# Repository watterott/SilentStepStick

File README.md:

# SilentStepStick
The Silent-Step-Stick is a Stepper Motor Driver Board for 2-Phase Motors based on [Trinamic](https://www.trinamic.com) Motor Drivers.

* Hardware compatible with [StepStick](https://reprap.org/wiki/StepStick) and [Pololu A4988](https://www.pololu.com/product/1182)
* [Trinamic](https://www.trinamic.com) stepper motor driver (chopper drive / constant current drive) with
  * Automatic standby current reduction
  * **microPlyer** - microstep interpolator for increased smoothness of microstepping
  * **stealthChop** - for quiet operation and smooth motion
  * **spreadCycle** - highly dynamic motor control chopper
* Open-Source and released under the [Creative Commons Attribution Share-Alike License](https://creativecommons.org/licenses/by-sa/4.0/).
* **[Documentation on learn.watterott.com](https://learn.watterott.com)**

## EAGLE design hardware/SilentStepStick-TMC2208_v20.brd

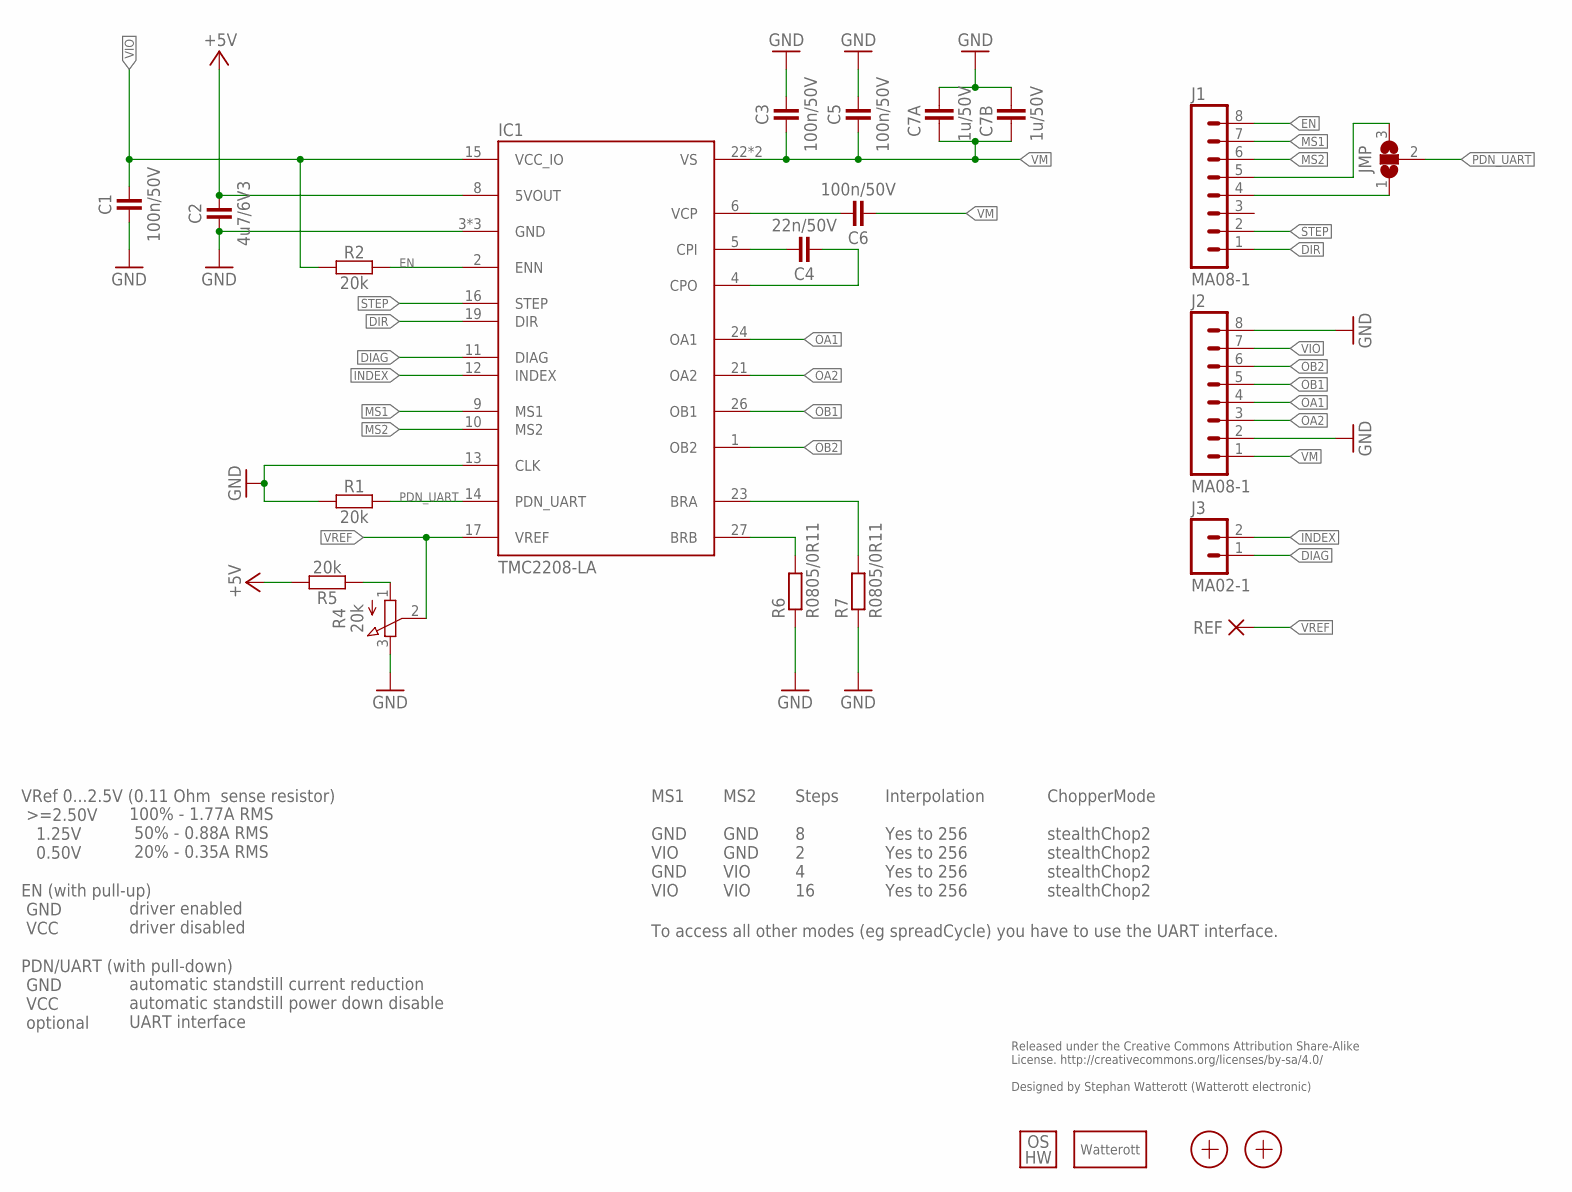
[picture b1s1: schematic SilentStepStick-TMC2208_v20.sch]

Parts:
C1, C3, C5, C6: 100n/50V; C0402
C2: 4u7/6V3; C0402
C4: 22n/50V; C0402
C7A: 1u/50V; C0805
C7B: 1u/50V; C1206
IC1: TMC2208-LA; QFN28-PAD
J1, J2: MA08-1
J3: MA02-1
JMP: JUMPER3-0402-NC; JUMPER3-0402_NC
LOGO3: LOGO_SPARK-2; SPARK_2MM
LOGO4: LOGO_OSHW-2; OSHW_2MM
R1, R2, R5: 20k; C0402
R4: 20k; POT_EVM3R
R6, R7: R0805/0R11; M0805
REF: PAD-0.6-1.1
X1, X2: PASSER-04; PASSER_04MM

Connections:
+5V: C2.2, IC1.8 (5VOUT), R5.2
BRA: IC1.23 (BRA), R7.2
BRB: IC1.27 (BRB), R6.2
CPI: C4.2, IC1.5 (CPI)
CPO: C4.1, IC1.4 (CPO)
DIAG: IC1.11 (DIAG), J3.1
DIR: IC1.19 (DIR), J1.1
EN: IC1.2 (ENN), J1.8, R2.2
GND: C1.1, C2.1, C3.2, C5.2, C7A.2, C7B.2, IC1.3 (GND), IC1.13 (CLK), IC1.18 (GND), IC1.TP (GND), J2.2, J2.8, R1.1, R4.3 (E), R6.1, R7.1
INDEX: IC1.12 (INDEX), J3.2
MS1: IC1.9 (MS1), J1.7
MS2: IC1.10 (MS2), J1.6
unnamed: J1.5, JMP.3
unnamed: J1.4, JMP.1
OA1: IC1.24 (OA1), J2.4
OA2: IC1.21 (OA2), J2.3
OB1: IC1.26 (OB1), J2.5
OB2: IC1.1 (OB2), J2.6
PDN_UART: IC1.14 (PDN_UART), JMP.2, R1.2
STEP: IC1.16 (STEP), J1.2
VCP: C6.2, IC1.6 (VCP)
VIO: C1.2, IC1.15 (VCC_IO), J2.7, R2.1
VM: C3.1, C5.1, C6.1, C7A.1, C7B.1, IC1.22 (VS), IC1.28 (VS), J2.1
VREF: IC1.17 (VREF), R4.2 (S), REF.1
VREF1: R4.1 (A), R5.1

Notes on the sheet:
Released under the Creative Commons Attribution Share-Alike License. http://creativecommons.org/licenses/by-sa/4.0/ Designed by Stephan Watterott (Watterott electronic)
VRef 0...2.5V (0.11 Ohm sense resistor) >=2.50V 1.25V 0.50V EN (with pull-up) GND VCC PDN/UART (with pull-down) GND VCC optional
100% - 1.77A RMS 50% - 0.88A RMS 20% - 0.35A RMS driver enabled driver disabled automatic standstill current reduction automatic standstill power down disable UART interface
MS1 GND VIO GND VIO
MS2 GND GND VIO VIO
Steps 8 2 4 16
Interpolation Yes to 256 Yes to 256 Yes to 256 Yes to 256
ChopperMode stealthChop2 stealthChop2 stealthChop2 stealthChop2
To access all other modes (eg spreadCycle) you have to use the UART interface.

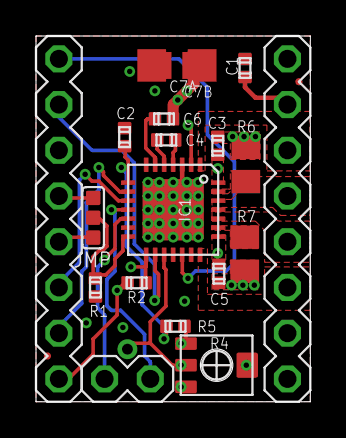
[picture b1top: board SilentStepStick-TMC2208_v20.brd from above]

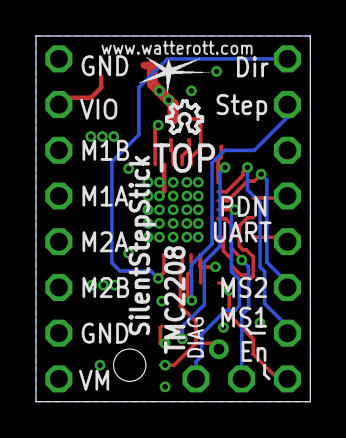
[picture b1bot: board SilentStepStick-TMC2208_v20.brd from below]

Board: 4 copper layers, 15.2 x 20.3 mm, 24 parts (2 on the bottom side), 25 nets.

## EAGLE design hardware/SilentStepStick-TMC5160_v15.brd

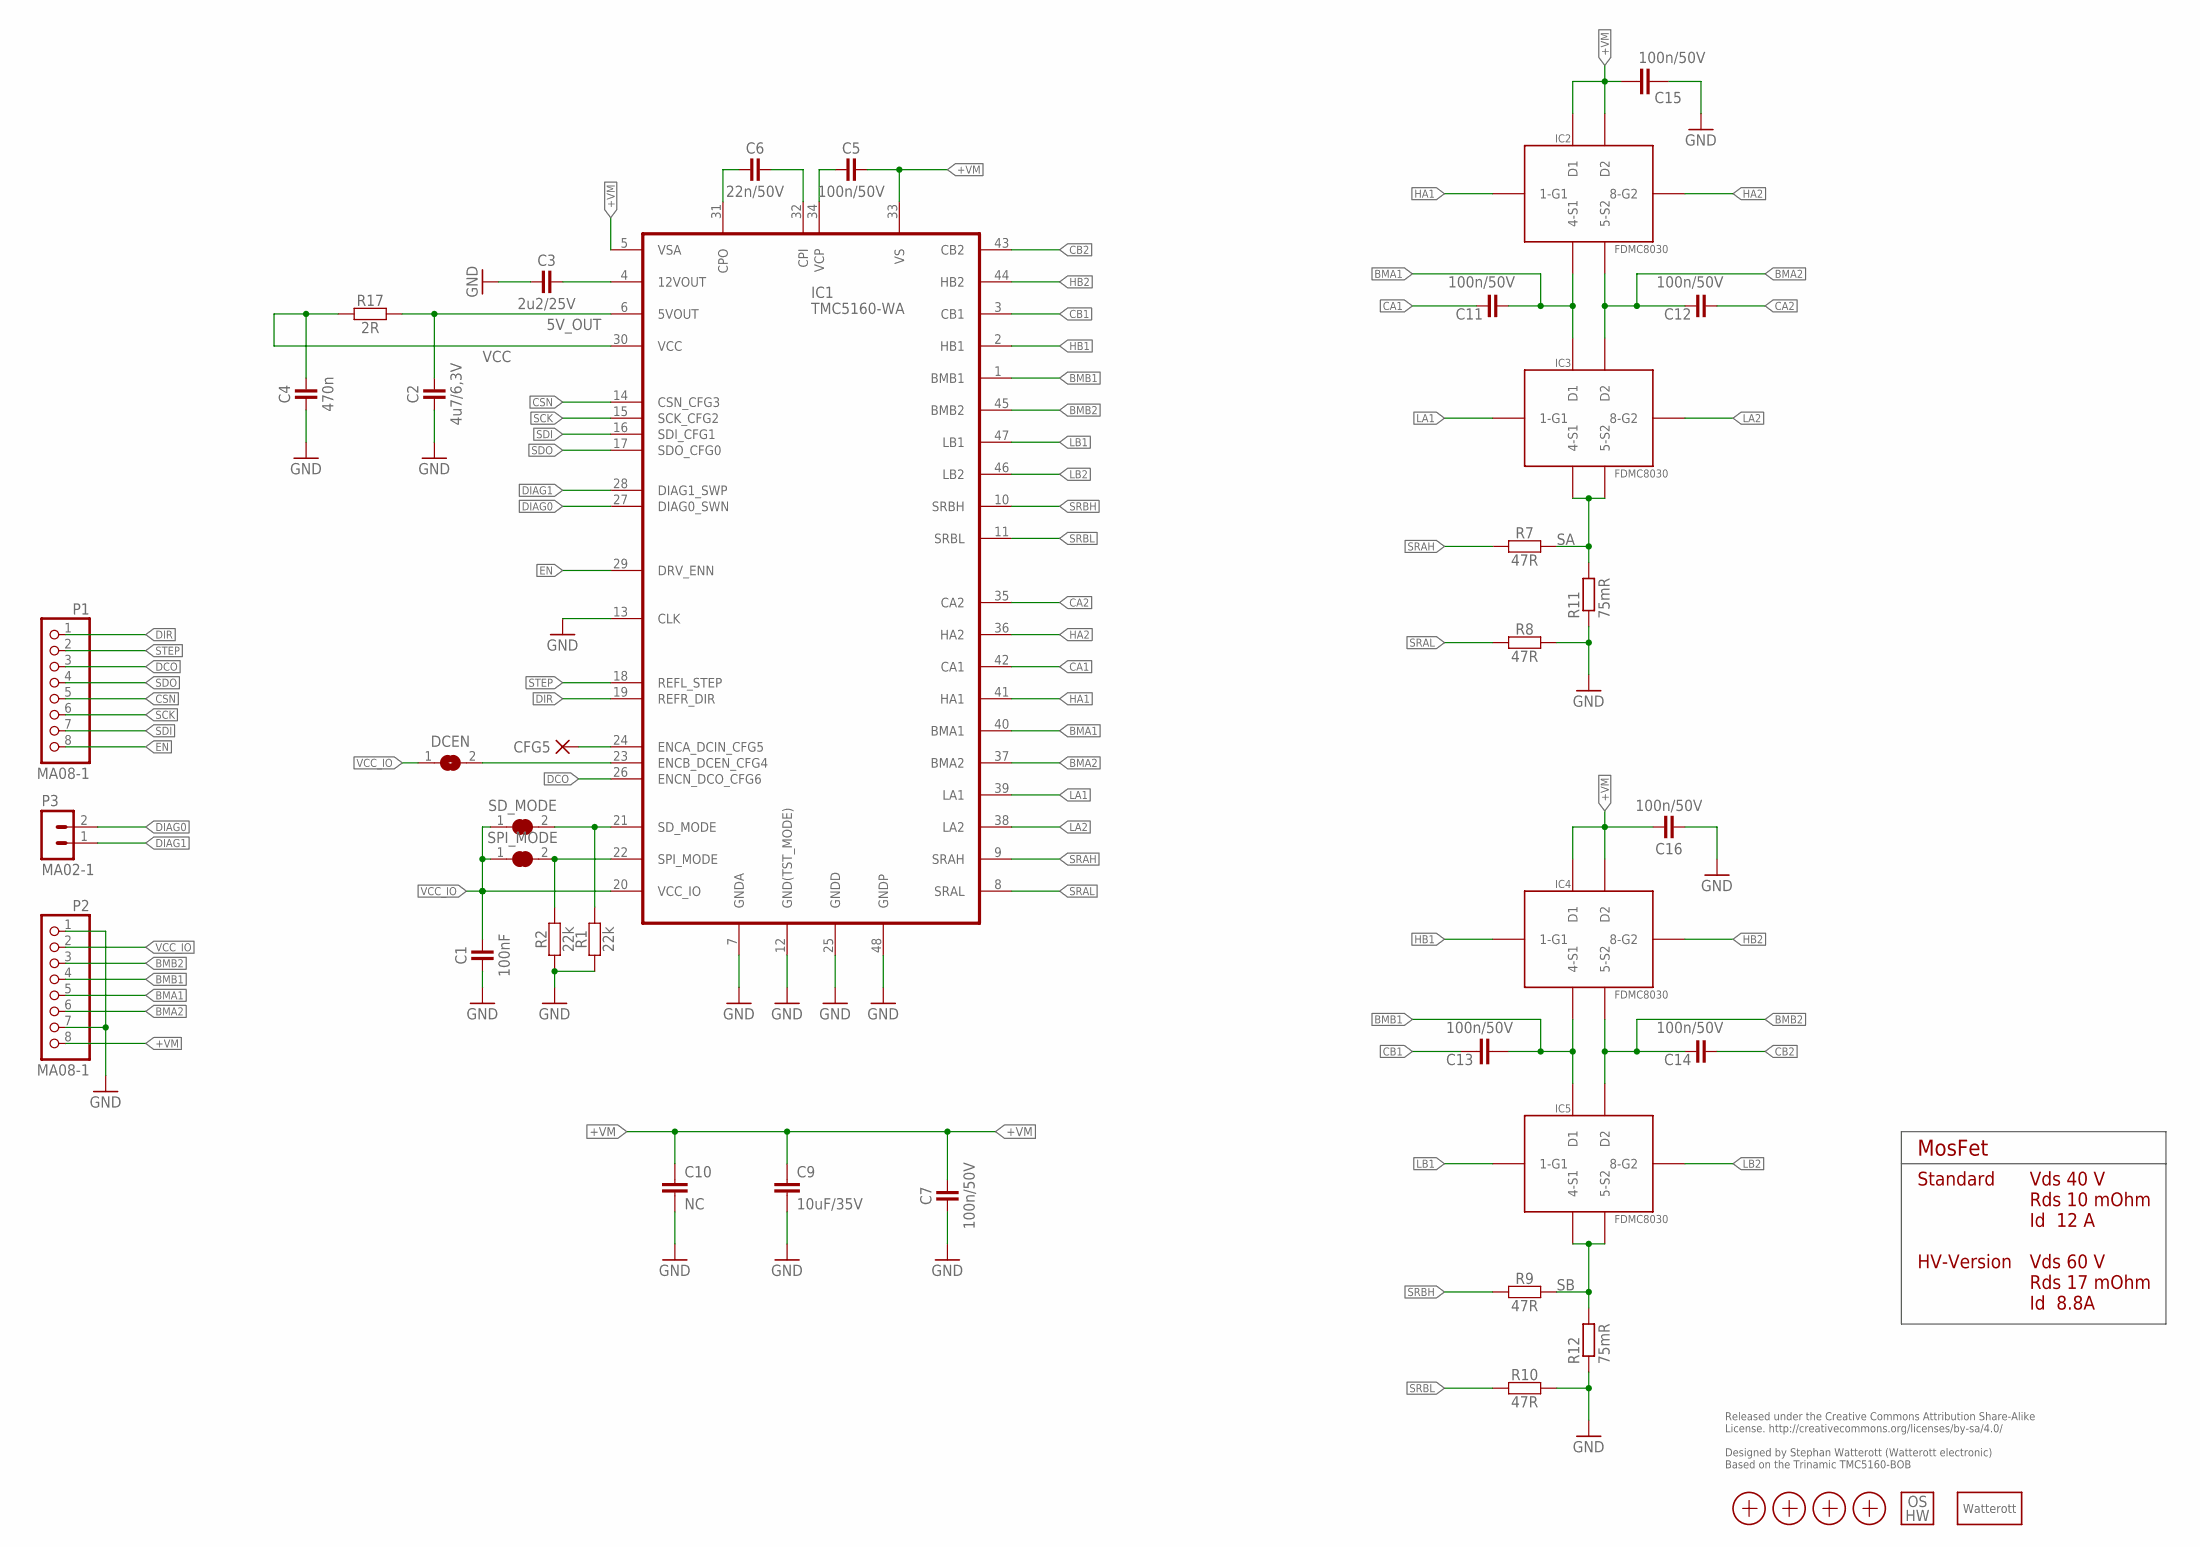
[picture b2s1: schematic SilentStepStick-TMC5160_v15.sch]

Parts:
C1: 100nF; C0402
C2: 4u7/6,3V; C0402
C3: 2u2/25V; C0402
C4: 470n; C0402
C5, C7, C11, C12, C13, C14, C15, C16: 100n/50V; C0402
C6: 22n/50V; C0402
C9: 10uF/35V; C0805
C10: NC; C0805
CFG5: PAD-0.7_NC
DCEN: JUMPER2-0402-NC; JUMPER2-0402_NC
IC1: TMC5160-WA; VQFN56(47)_8.0X8.0X0.9MM_0.5P_EP
IC2, IC3, IC4, IC5: FDMC8030; 8-POWERWDFN
LOGO1: LOGO_SPARK-2; SPARK_2MM
LOGO2: LOGO_OSHW-2; OSHW_2MM
P1, P2: MA08-1; 1X08-S
P3: MA02-1
R1, R2: 22k; C0201
R7, R8, R9, R10: 47R; C0402
R11, R12: 75mR; R1206
R17: 2R; C0402
SD_MODE: JUMPER2-0402-NC; JUMPER2-0402_NC
SPI_MODE: JUMPER2-0402-NC; JUMPER2-0402_NC
X1, X2, X3, X4: PASSER-04; PASSER_04MM

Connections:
5V_OUT: C2.2, IC1.6 (5VOUT), R17.2
+VM: C5.2, C7.2, C9.1, C10.1, C15.2, C16.2, IC1.5 (VSA), IC1.33 (VS), IC2.P$D1 (D1), IC2.P$D2 (D2), IC4.P$D1 (D1), IC4.P$D2 (D2), P2.8
BMA1: C11.1, IC1.40 (BMA1), IC2.P$4 (4-S1), IC3.P$D1 (D1), P2.5
BMA2: C12.2, IC1.37 (BMA2), IC2.P$5 (5-S2), IC3.P$D2 (D2), P2.6
BMB1: C13.1, IC1.1 (BMB1), IC4.P$4 (4-S1), IC5.P$D1 (D1), P2.4
BMB2: C14.2, IC1.45 (BMB2), IC4.P$5 (5-S2), IC5.P$D2 (D2), P2.3
CA1: C11.2, IC1.42 (CA1)
CA2: C12.1, IC1.35 (CA2)
CB1: C13.2, IC1.3 (CB1)
CB2: C14.1, IC1.43 (CB2)
CSN: IC1.14 (CSN_CFG3), P1.5
DCEN: DCEN.2, IC1.23 (ENCB_DCEN_CFG4)
DCIN: CFG5.1, IC1.24 (ENCA_DCIN_CFG5)
DCO: IC1.26 (ENCN_DCO_CFG6), P1.3
DIAG0: IC1.27 (DIAG0_SWN), P3.2
DIAG1: IC1.28 (DIAG1_SWP), P3.1
DIR: IC1.19 (REFR_DIR), P1.1
EN: IC1.29 (DRV_ENN), P1.8
GND: C1.1, C2.1, C3.1, C4.1, C7.1, C9.2, C10.2, C15.1, C16.1, IC1.7 (GNDA), IC1.12 (GND(TST_MODE)), IC1.13 (CLK), IC1.25 (GNDD), IC1.48 (GNDP), P2.1, P2.7, R1.1, R2.1, R8.2, R10.2, R11.1, R12.1
HA1: IC1.41 (HA1), IC2.P$1 (1-G1)
HA2: IC1.36 (HA2), IC2.P$8 (8-G2)
HB1: IC1.2 (HB1), IC4.P$1 (1-G1)
HB2: IC1.44 (HB2), IC4.P$8 (8-G2)
LA1: IC1.39 (LA1), IC3.P$1 (1-G1)
LA2: IC1.38 (LA2), IC3.P$8 (8-G2)
LB1: IC1.47 (LB1), IC5.P$1 (1-G1)
LB2: IC1.46 (LB2), IC5.P$8 (8-G2)
unnamed: C6.2, IC1.32 (CPI)
unnamed: C6.1, IC1.31 (CPO)
unnamed: C3.2, IC1.4 (12VOUT)
unnamed: C5.1, IC1.34 (VCP)
SA: IC3.P$4 (4-S1), IC3.P$5 (5-S2), R7.2, R11.2
SB: IC5.P$4 (4-S1), IC5.P$5 (5-S2), R9.2, R12.2
SCK: IC1.15 (SCK_CFG2), P1.6
SD: IC1.21 (SD_MODE), R1.2, SD_MODE.2
SDI: IC1.16 (SDI_CFG1), P1.7
SDO: IC1.17 (SDO_CFG0), P1.4
SPI: IC1.22 (SPI_MODE), R2.2, SPI_MODE.2
SRAH: IC1.9 (SRAH), R7.1
SRAL: IC1.8 (SRAL), R8.1
SRBH: IC1.10 (SRBH), R9.1
SRBL: IC1.11 (SRBL), R10.1
STEP: IC1.18 (REFL_STEP), P1.2
VCC: C4.2, IC1.30 (VCC), R17.1
VCC_IO: C1.2, DCEN.1, IC1.20 (VCC_IO), P2.2, SD_MODE.1, SPI_MODE.1

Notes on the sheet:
Released under the Creative Commons Attribution Share-Alike License. http://creativecommons.org/licenses/by-sa/4.0/ Designed by Stephan Watterott (Watterott electronic) Based on the Trinamic TMC5160-BOB
Vds 40 V Rds 10 mOhm Id 12 A Vds 60 V Rds 17 mOhm Id 8.8A
MosFet
Standard HV-Version

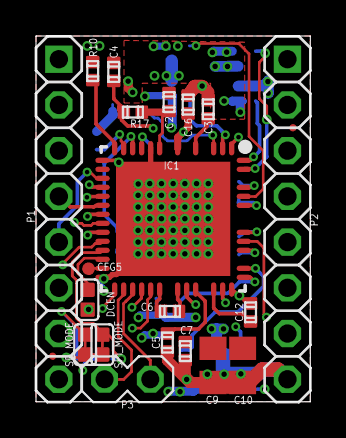
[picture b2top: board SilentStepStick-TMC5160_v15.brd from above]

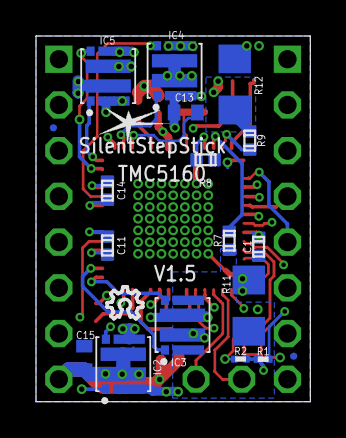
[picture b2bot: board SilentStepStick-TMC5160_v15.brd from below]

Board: 6 copper layers, 15.2 x 20.3 mm, 42 parts (20 on the bottom side), 45 nets.

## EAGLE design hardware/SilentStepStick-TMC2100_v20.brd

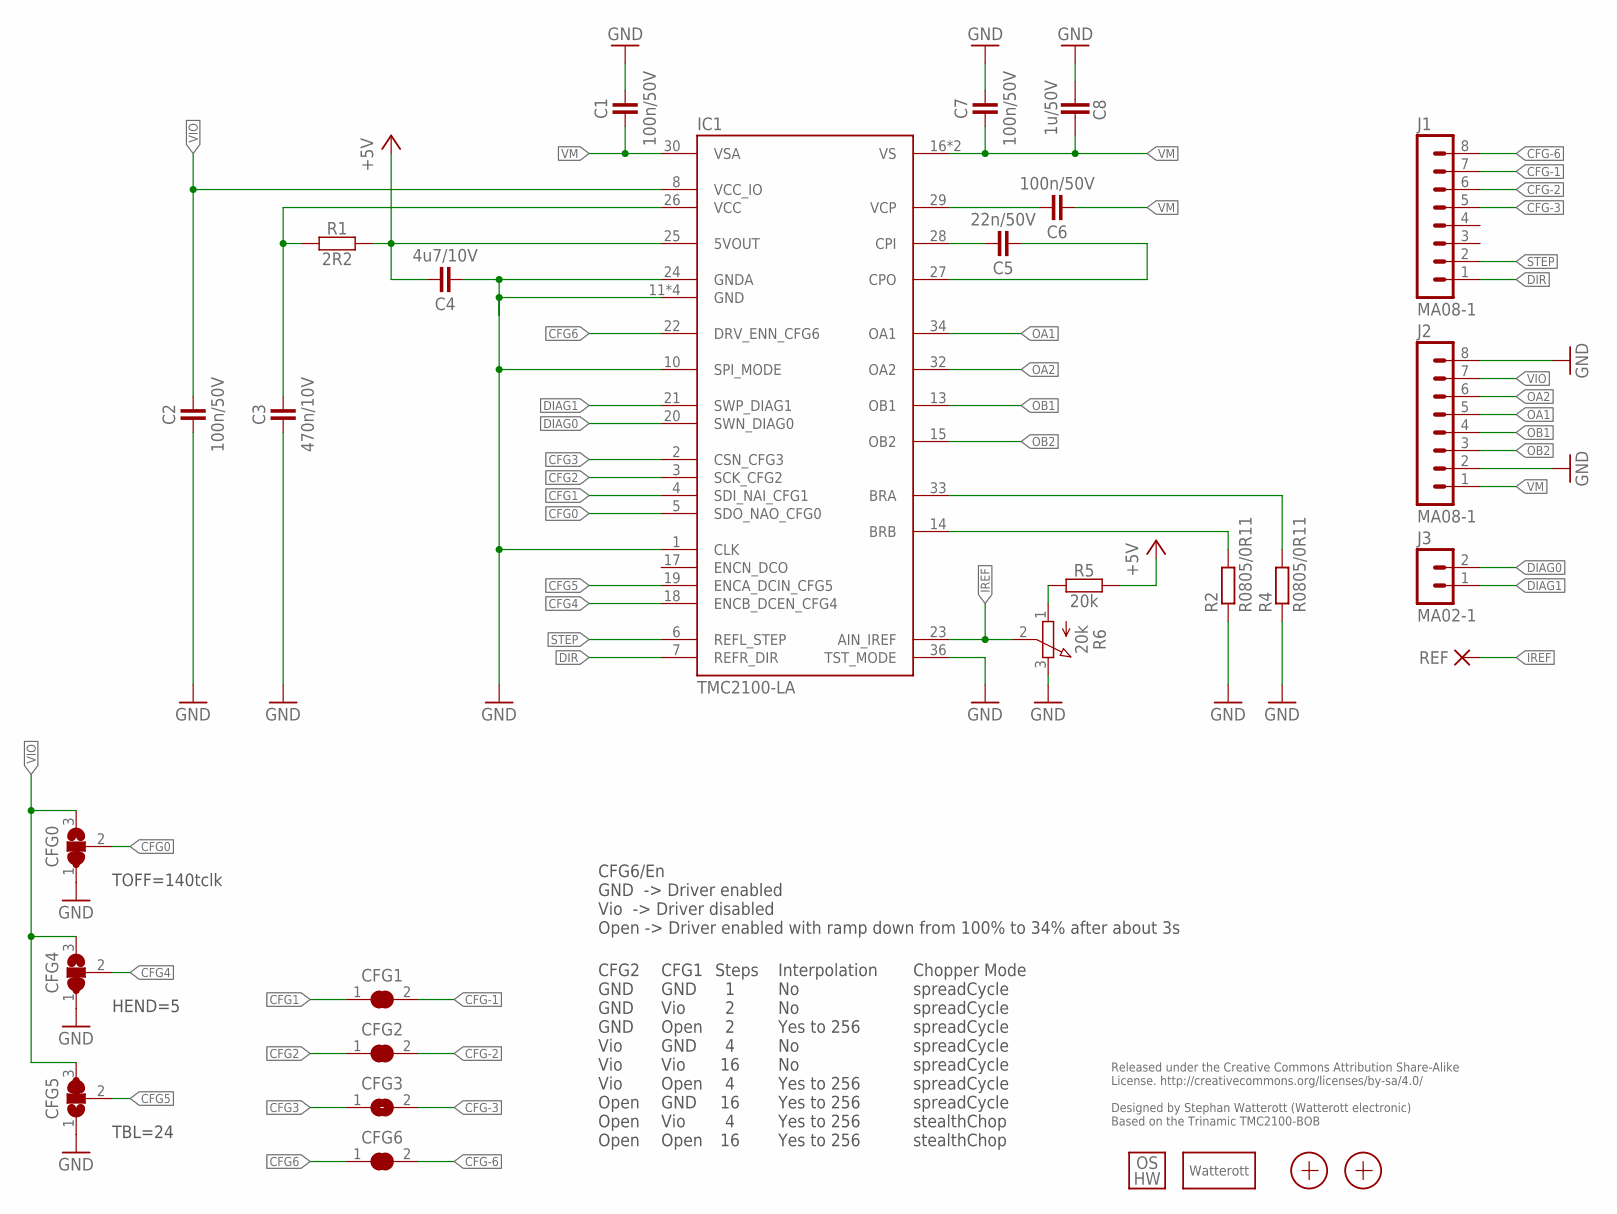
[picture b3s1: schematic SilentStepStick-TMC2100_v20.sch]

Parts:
C1, C2, C6, C7: 100n/50V; C0402
C3: 470n/10V; C0402
C4: 4u7/10V; C0402
C5: 22n/50V; C0402
C8: 1u/50V; C0603
CFG0, CFG4, CFG5: JUMPER3-0201
CFG1, CFG2, CFG3, CFG6: JUMPER2-0201
IC1: TMC2100-LA; QFN36-PAD
J1, J2: MA08-1
J3: MA02-1
LOGO3: LOGO_SPARK-2; SPARK_2MM
LOGO4: LOGO_OSHW-2; OSHW_2MM
R1: 2R2; C0402
R2, R4: R0805/0R11; M0805
R5: 20k; C0402
R6: 20k; POT_EVM3R
REF: PAD-0.6-1.1
X1, X2: PASSER-07; PASSER_07MM

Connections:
+5V: C4.2, IC1.25 (5VOUT), R1.2, R5.2
BRA: IC1.33 (BRA), R4.2
BRB: IC1.14 (BRB), R2.2
CFG0: CFG0.2, IC1.5 (SDO_NAO_CFG0)
CFG1: CFG1.1, IC1.4 (SDI_NAI_CFG1)
CFG2: CFG2.1, IC1.3 (SCK_CFG2)
CFG3: CFG3.1, IC1.2 (CSN_CFG3)
CFG4: CFG4.2, IC1.18 (ENCB_DCEN_CFG4)
CFG5: CFG5.2, IC1.19 (ENCA_DCIN_CFG5)
CFG6: CFG6.1, IC1.22 (DRV_ENN_CFG6)
CFG-1: CFG1.2, J1.7
CFG-2: CFG2.2, J1.6
CFG-3: CFG3.2, J1.5
CFG-6: CFG6.2, J1.8
CPI: C5.2, IC1.28 (CPI)
CPO: C5.1, IC1.27 (CPO)
DIAG0: IC1.20 (SWN_DIAG0), J3.2
DIAG1: IC1.21 (SWP_DIAG1), J3.1
DIR: IC1.7 (REFR_DIR), J1.1
GND: C1.2, C2.1, C3.1, C4.1, C7.2, C8.2, CFG0.1, CFG4.1, CFG5.1, IC1.1 (CLK), IC1.10 (SPI_MODE), IC1.11 (GND), IC1.12 (GND), IC1.24 (GNDA), IC1.35 (GND), IC1.36 (TST_MODE), IC1.TP (GND), J2.2, J2.8, R2.1, R4.1, R6.3 (E)
IREF: IC1.23 (AIN_IREF), R6.2 (S), REF.1
OA1: IC1.34 (OA1), J2.5
OA2: IC1.32 (OA2), J2.6
OB1: IC1.13 (OB1), J2.4
OB2: IC1.15 (OB2), J2.3
STEP: IC1.6 (REFL_STEP), J1.2
VCC: C3.2, IC1.26 (VCC), R1.1
VCP: C6.2, IC1.29 (VCP)
VIO: C2.2, CFG0.3, CFG4.3, CFG5.3, IC1.8 (VCC_IO), J2.7
VM: C1.1, C6.1, C7.1, C8.1, IC1.16 (VS), IC1.30 (VSA), IC1.31 (VS), J2.1
VREF1: R5.1, R6.1 (A)

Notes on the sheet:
Released under the Creative Commons Attribution Share-Alike License. http://creativecommons.org/licenses/by-sa/4.0/ Designed by Stephan Watterott (Watterott electronic) Based on the Trinamic TMC2100-BOB
CFG6/En GND -> Driver enabled Vio -> Driver disabled Open -> Driver enabled with ramp down from 100% to 34% after about 3s
CFG2 GND GND GND Vio Vio Vio Open Open Open
CFG1 GND Vio Open GND Vio Open GND Vio Open
Steps 1 2 2 4 16 4 16 4 16
Interpolation No No Yes to 256 No No Yes to 256 Yes to 256 Yes to 256 Yes to 256
Chopper Mode spreadCycle spreadCycle spreadCycle spreadCycle spreadCycle spreadCycle spreadCycle stealthChop stealthChop
TOFF=140tclk
HEND=5
TBL=24

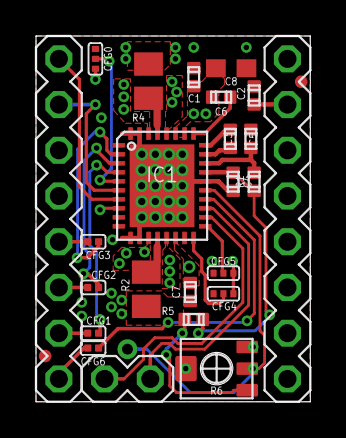
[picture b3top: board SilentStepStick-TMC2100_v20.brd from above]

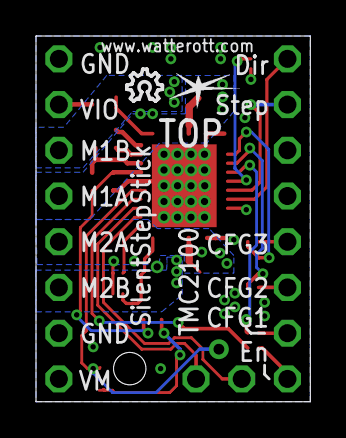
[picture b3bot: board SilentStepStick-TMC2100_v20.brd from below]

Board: 4 copper layers, 15.2 x 20.3 mm, 29 parts (2 on the bottom side), 31 nets.

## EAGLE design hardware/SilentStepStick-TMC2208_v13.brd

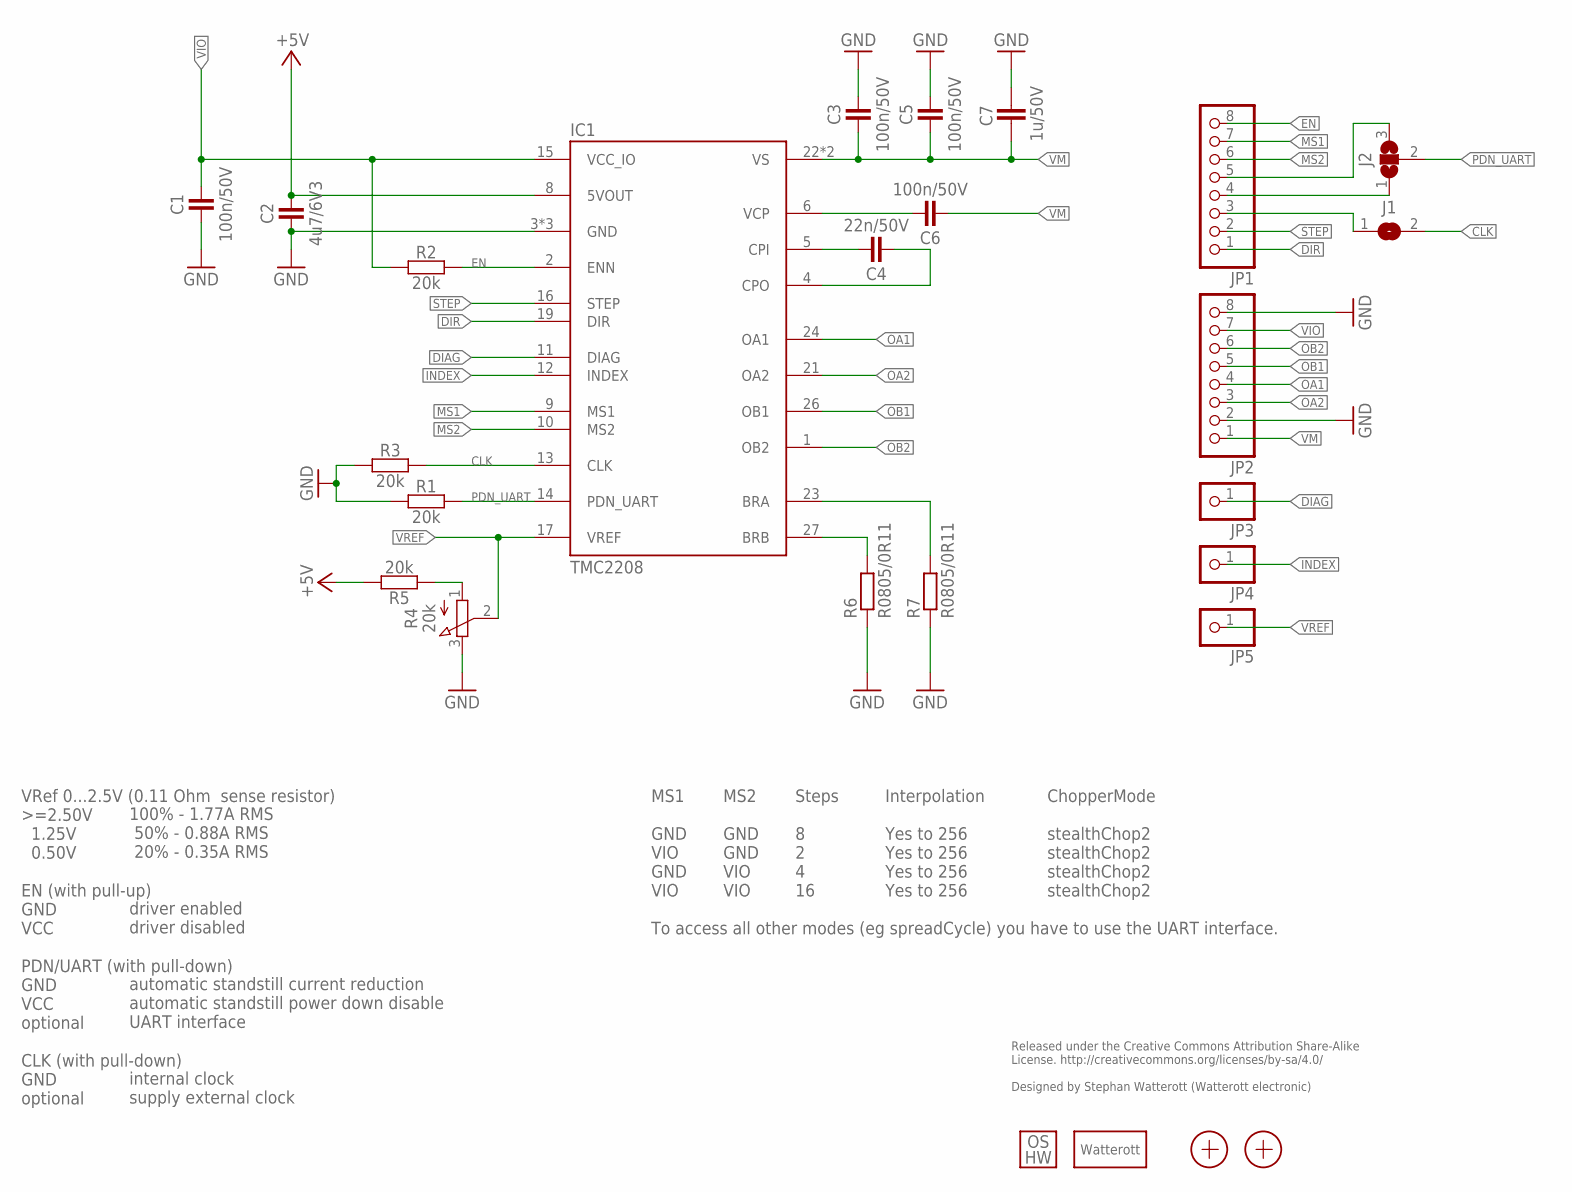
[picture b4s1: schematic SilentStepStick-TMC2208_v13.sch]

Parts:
C1, C3, C5, C6: 100n/50V; C0402
C2: 4u7/6V3; C0402
C4: 22n/50V; C0402
C7: 1u/50V; C0805
IC1: TMC2208; QFN28-PAD
J1: JUMPER2-0402
J2: JUMPER3-0402-NC; JUMPER3-0402_NC
JP1, JP2: PINHD-1X08_2.54-S; 1X08-S
JP3, JP4, JP5: PINHD-1X1; 1X01
LOGO3: LOGO_SPARK-2; SPARK_2MM
LOGO4: LOGO_OSHW-2; OSHW_2MM
R1, R2, R3, R5: 20k; C0402
R4: 20k; POT_EVM3R
R6, R7: R0805/0R11; M0805
X1, X2: PASSER-04; PASSER_04MM

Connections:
+5V: C2.2, IC1.8 (5VOUT), R5.2
BRA: IC1.23 (BRA), R7.2
BRB: IC1.27 (BRB), R6.2
CLK: IC1.13 (CLK), J1.2, R3.2
CPI: C4.2, IC1.5 (CPI)
CPO: C4.1, IC1.4 (CPO)
DIAG: IC1.11 (DIAG), JP3.1
DIR: IC1.19 (DIR), JP1.1
EN: IC1.2 (ENN), JP1.8, R2.2
GND: C1.1, C2.1, C3.2, C5.2, C7.2, IC1.3 (GND), IC1.18 (GND), IC1.TP (GND), JP2.2, JP2.8, R1.1, R3.1, R4.3 (E), R6.1, R7.1
INDEX: IC1.12 (INDEX), JP4.1
MS1: IC1.9 (MS1), JP1.7
MS2: IC1.10 (MS2), JP1.6
unnamed: J2.3, JP1.5
unnamed: J1.1, JP1.3
unnamed: J2.1, JP1.4
OA1: IC1.24 (OA1), JP2.4
OA2: IC1.21 (OA2), JP2.3
OB1: IC1.26 (OB1), JP2.5
OB2: IC1.1 (OB2), JP2.6
PDN_UART: IC1.14 (PDN_UART), J2.2, R1.2
STEP: IC1.16 (STEP), JP1.2
VCP: C6.2, IC1.6 (VCP)
VIO: C1.2, IC1.15 (VCC_IO), JP2.7, R2.1
VM: C3.1, C5.1, C6.1, C7.1, IC1.22 (VS), IC1.28 (VS), JP2.1
VREF: IC1.17 (VREF), JP5.1, R4.2 (S)
VREF1: R4.1 (A), R5.1

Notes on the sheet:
Released under the Creative Commons Attribution Share-Alike License. http://creativecommons.org/licenses/by-sa/4.0/ Designed by Stephan Watterott (Watterott electronic)
VRef 0...2.5V (0.11 Ohm sense resistor) >=2.50V 1.25V 0.50V EN (with pull-up) GND VCC PDN/UART (with pull-down) GND VCC optional CLK (with pull-down) GND optional
100% - 1.77A RMS 50% - 0.88A RMS 20% - 0.35A RMS driver enabled driver disabled automatic standstill current reduction automatic standstill power down disable UART interface internal clock supply external clock
MS1 GND VIO GND VIO To access all other modes (eg spreadCycle) you have to use the UART interface.
MS2 GND GND VIO VIO
Steps 8 2 4 16
Interpolation Yes to 256 Yes to 256 Yes to 256 Yes to 256
ChopperMode stealthChop2 stealthChop2 stealthChop2 stealthChop2

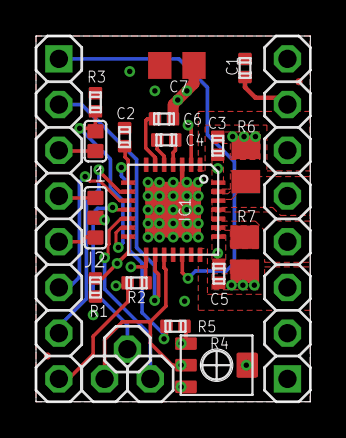
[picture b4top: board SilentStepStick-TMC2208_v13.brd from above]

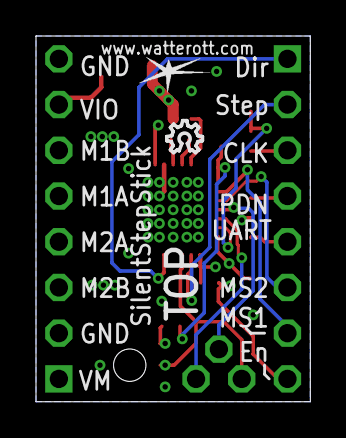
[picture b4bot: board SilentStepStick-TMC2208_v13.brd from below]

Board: 4 copper layers, 15.2 x 20.3 mm, 26 parts (2 on the bottom side), 27 nets.

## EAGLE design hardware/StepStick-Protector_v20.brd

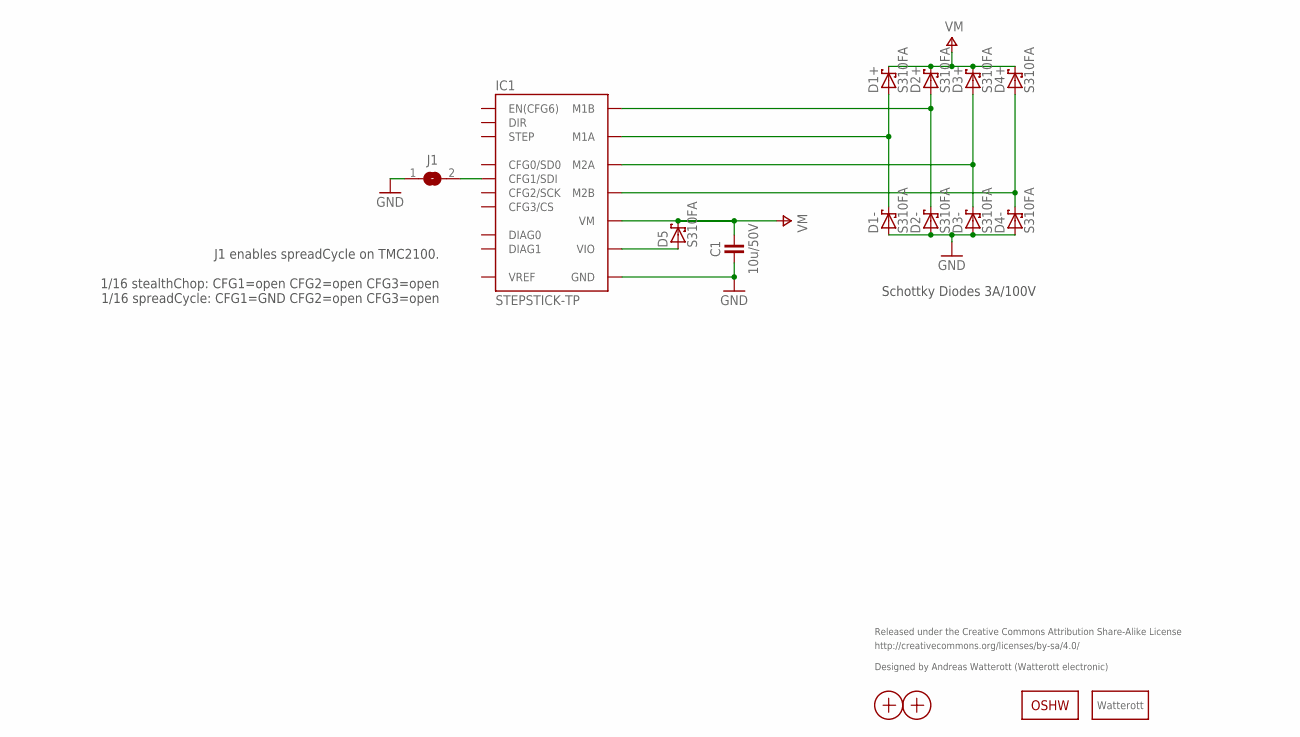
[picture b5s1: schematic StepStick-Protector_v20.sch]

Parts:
C1: 10u/50V; C1210
D1+, D1-, D2+, D2-, D3+, D3-, D4+, D4-, D5: S310FA; SOD123
IC1: STEPSTICK-TP; STEPSTICK_TP
J1: JUMPER2-0603-NC; JUMPER2-0603_NC
LOGO1: OSHW_LOGOX0070; OSHW_6X70
LOGO3: LOGO_SPARK-2; SPARK_2MM
X1, X2: PASSER

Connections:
GND: C1.1, D1-.A, D2-.A, D3-.A, D4-.A, IC1.GND@1 (GND), IC1.GND@2 (GND), J1.1
M1A: D1+.A, D1-.C, IC1.M1A
M1B: D2+.A, D2-.C, IC1.M1B
M2A: D3+.A, D3-.C, IC1.M2A
M2B: D4+.A, D4-.C, IC1.M2B
unnamed: IC1.CFG1 (CFG1/SDI), J1.2
VIO: D5.A, IC1.VIO
VM: C1.2, D1+.C, D2+.C, D3+.C, D4+.C, D5.C, IC1.VM

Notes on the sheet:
Released under the Creative Commons Attribution Share-Alike License
http://creativecommons.org/licenses/by-sa/4.0/
Designed by Andreas Watterott (Watterott electronic)
Schottky Diodes 3A/100V
J1 enables spreadCycle on TMC2100. 1/16 stealthChop: CFG1=open CFG2=open CFG3=open 1/16 spreadCycle: CFG1=GND CFG2=open CFG3=open

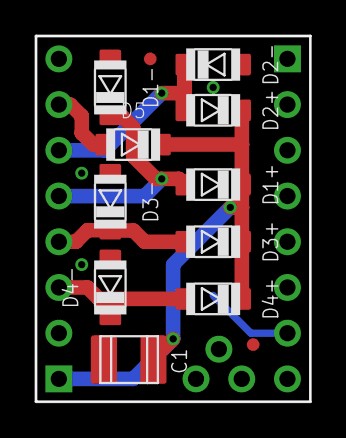
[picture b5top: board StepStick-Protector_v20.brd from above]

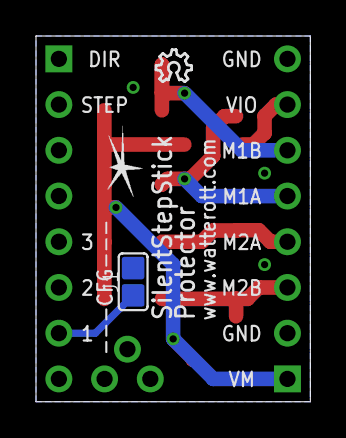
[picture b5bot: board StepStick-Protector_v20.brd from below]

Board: 2 copper layers, 15.2 x 20.3 mm, 16 parts (3 on the bottom side), 8 nets.

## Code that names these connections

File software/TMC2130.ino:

/*
  SilentStepStick TMC2130 Example
  Rsense: 0.11 Ohm

  Other examples/libraries can be found here:
  https://github.com/teemuatlut/TMCStepper
  https://github.com/trinamic/TMC-API
  https://github.com/janelia-arduino/TMC2130
  https://github.com/makertum/Trinamic_TMC2130

  Example source code free to use.
  Further information: https://learn.watterott.com/license/
*/

#include <SPI.h>

// Note: You also have to connect GND, 5V/VIO and VM.
//       A connection diagram can be found in the schematics.
#define EN_PIN    7 //enable (CFG6)
#define DIR_PIN   8 //direction
#define STEP_PIN  9 //step

#define CS_PIN   10 //CS chip select
#define MOSI_PIN 11 //SDI/MOSI (ICSP: 4, Uno: 11, Mega: 51)
#define MISO_PIN 12 //SDO/MISO (ICSP: 1, Uno: 12, Mega: 50)
#define SCK_PIN  13 //CLK/SCK  (ICSP: 3, Uno: 13, Mega: 52)

//TMC2130 registers
#define WRITE_FLAG     (1<<7) //write flag
#define READ_FLAG      (0<<7) //read flag
#define REG_GCONF      0x00
#define REG_GSTAT      0x01
#define REG_IHOLD_IRUN 0x10
#define REG_CHOPCONF   0x6C
#define REG_COOLCONF   0x6D
#define REG_DCCTRL     0x6E
#define REG_DRVSTATUS  0x6F

uint8_t tmc_write(uint8_t cmd, uint32_t data)
{
  uint8_t s;

  digitalWrite(CS_PIN, LOW);

  s = SPI.transfer(cmd);
  SPI.transfer((data>>24UL)&0xFF);
  SPI.transfer((data>>16UL)&0xFF);
  SPI.transfer((data>> 8UL)&0xFF);
  SPI.transfer((data>> 0UL)&0xFF);

  digitalWrite(CS_PIN, HIGH);

  return s;
}

uint8_t tmc_read(uint8_t cmd, uint32_t *data)
{
  uint8_t s;

  tmc_write(cmd, 0UL); //set read address

  digitalWrite(CS_PIN, LOW);

  s = SPI.transfer(cmd);
  *data  = SPI.transfer(0x00)&0xFF;
  *data <<=8;
  *data |= SPI.transfer(0x00)&0xFF;
  *data <<=8;
  *data |= SPI.transfer(0x00)&0xFF;
  *data <<=8;
  *data |= SPI.transfer(0x00)&0xFF;

  digitalWrite(CS_PIN, HIGH);

  return s;
}

void setup()
{
  //set pins
  pinMode(EN_PIN, OUTPUT);
  digitalWrite(EN_PIN, HIGH); //deactivate driver (LOW active)
  pinMode(DIR_PIN, OUTPUT);
  digitalWrite(DIR_PIN, LOW); //LOW or HIGH
  pinMode(STEP_PIN, OUTPUT);
  digitalWrite(STEP_PIN, LOW);

  pinMode(CS_PIN, OUTPUT);
  digitalWrite(CS_PIN, HIGH);
  pinMode(MOSI_PIN, OUTPUT);
  digitalWrite(MOSI_PIN, LOW);
  pinMode(MISO_PIN, INPUT);
  digitalWrite(MISO_PIN, HIGH);
  pinMode(SCK_PIN, OUTPUT);
  digitalWrite(SCK_PIN, LOW);

  //init serial port
  Serial.begin(9600); //init serial port and set baudrate
  while(!Serial); //wait for serial port to connect (needed for Leonardo only)
  Serial.println("\nStart...");

  //init SPI
  SPI.begin();
  //SPI.setDataMode(SPI_MODE3); //SPI Mode 3
  //SPI.setBitOrder(MSBFIRST); //MSB first
  //SPI.setClockDivider(SPI_CLOCK_DIV128); //clk=Fcpu/128
  SPI.beginTransaction(SPISettings(1000000UL, MSBFIRST, SPI_MODE3));

  //set TMC2130 config
  tmc_write(WRITE_FLAG|REG_GCONF,      0x00000001UL); //voltage on AIN is current reference
  tmc_write(WRITE_FLAG|REG_IHOLD_IRUN, 0x00001010UL); //IHOLD=0x10, IRUN=0x10
  tmc_write(WRITE_FLAG|REG_CHOPCONF,   0x00008008UL); //native 256 microsteps, MRES=0, TBL=1=24, TOFF=8
  //tmc_write(WRITE_FLAG|REG_CHOPCONF,   0x01008008UL); //128 microsteps, MRES=0, TBL=1=24, TOFF=8
  //tmc_write(WRITE_FLAG|REG_CHOPCONF,   0x02008008UL); // 64 microsteps, MRES=0, TBL=1=24, TOFF=8
  //tmc_write(WRITE_FLAG|REG_CHOPCONF,   0x03008008UL); // 32 microsteps, MRES=0, TBL=1=24, TOFF=8
  //tmc_write(WRITE_FLAG|REG_CHOPCONF,   0x04008008UL); // 16 microsteps, MRES=0, TBL=1=24, TOFF=8
  //tmc_write(WRITE_FLAG|REG_CHOPCONF,   0x05008008UL); //  8 microsteps, MRES=0, TBL=1=24, TOFF=8
  //tmc_write(WRITE_FLAG|REG_CHOPCONF,   0x06008008UL); //  4 microsteps, MRES=0, TBL=1=24, TOFF=8
  //tmc_write(WRITE_FLAG|REG_CHOPCONF,   0x07008008UL); //  2 microsteps, MRES=0, TBL=1=24, TOFF=8
  //tmc_write(WRITE_FLAG|REG_CHOPCONF,   0x08008008UL); //  1 microsteps, MRES=0, TBL=1=24, TOFF=8

  //outputs on (LOW active)
  digitalWrite(EN_PIN, LOW);
}

void loop()
{
  static uint32_t last_time=0;
  uint32_t ms = millis();
  uint32_t data;
  uint8_t s;
    
  if((ms-last_time) > 1000) //run every 1s
  {
    last_time = ms;

    //show REG_GSTAT
    s = tmc_read(REG_GSTAT, &data);
    Serial.print("GSTAT:     0x0");
    Serial.print(data, HEX);
    Serial.print("\t - ");
    Serial.print("Status: 0x");
    Serial.print(s, HEX);
    if(s & 0x01) Serial.print(" reset");
    if(s & 0x02) Serial.print(" error");
    if(s & 0x04) Serial.print(" sg2");
    if(s & 0x08) Serial.print(" standstill");
    Serial.println(" ");

    //show REG_DRVSTATUS
    s = tmc_read(REG_DRVSTATUS, &data);
    Serial.print("DRVSTATUS: 0x");
    Serial.print(data, HEX);
    Serial.print("\t - ");
    Serial.print("Status: 0x");
    Serial.print(s, HEX);
    if(s & 0x01) Serial.print(" reset");
    if(s & 0x02) Serial.print(" error");
    if(s & 0x04) Serial.print(" sg2");
    if(s & 0x08) Serial.print(" standstill");
    Serial.println(" ");
  }

  //make steps
  digitalWrite(STEP_PIN, HIGH);
  delayMicroseconds(10);
  digitalWrite(STEP_PIN, LOW);
  delayMicroseconds(10);
}

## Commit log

2017-02-28 added TMC2208 Configurator
2017-03-01 added StepStick-Tester
2017-03-01 renamed files
2017-03-21 updated TMC2208 script
2017-04-10 updated layout
2017-04-10 added SilentStepStick TMC2208 v1.1
2017-04-12 updated schematics
2017-04-16 updated docu
2017-04-16 added TMC2208 Configurator sce file
2017-04-16 updated examples
2017-04-28 updated screenshot
2017-05-30 updated dou
2017-07-30 moved docu to docs
2017-07-31 moved TMC2208 Configurator to docs
2017-10-09 updated software example
2017-11-12 updated docuz
2017-12-02 added SilentStepStick TMC2100 v1.3
2018-01-09 updated pdf
2018-01-13 updated schematics and layout files
2018-01-30 moved files
2018-02-28 added v2 Protector
2018-11-05 added TMC2208 v1.3
2019-02-24 added TMC5160
2019-05-11 added TMC2100 5V v2.0
2019-06-11 added TMC2209 v2.0
2019-06-24 updated script
2019-06-24 added script for TMC2208+TMC2209
2019-07-05 added TMC2130 v2.0
2019-07-05 updated silkscreen
2019-07-15 added SilentStepStick TMC5160 v1.4
2019-10-02 updated error messages
2019-10-29 updated scripts
2019-11-26 updated software examples
2020-01-20 added TMC2100 v2
2020-05-11 added license
2020-05-30 updated license
2020-05-30 added TMC5160 v1.5
2021-02-14 OTP register bugfix
2021-02-14 typo fix
2021-02-14 slave address info
2021-09-27 added TMC2208 v2.0
2022-02-27 corrected Vref and current values
